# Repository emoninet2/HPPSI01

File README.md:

# HPPSI01

link to [HPPSI02](https://github.com/emoninet2/HPPSI02)

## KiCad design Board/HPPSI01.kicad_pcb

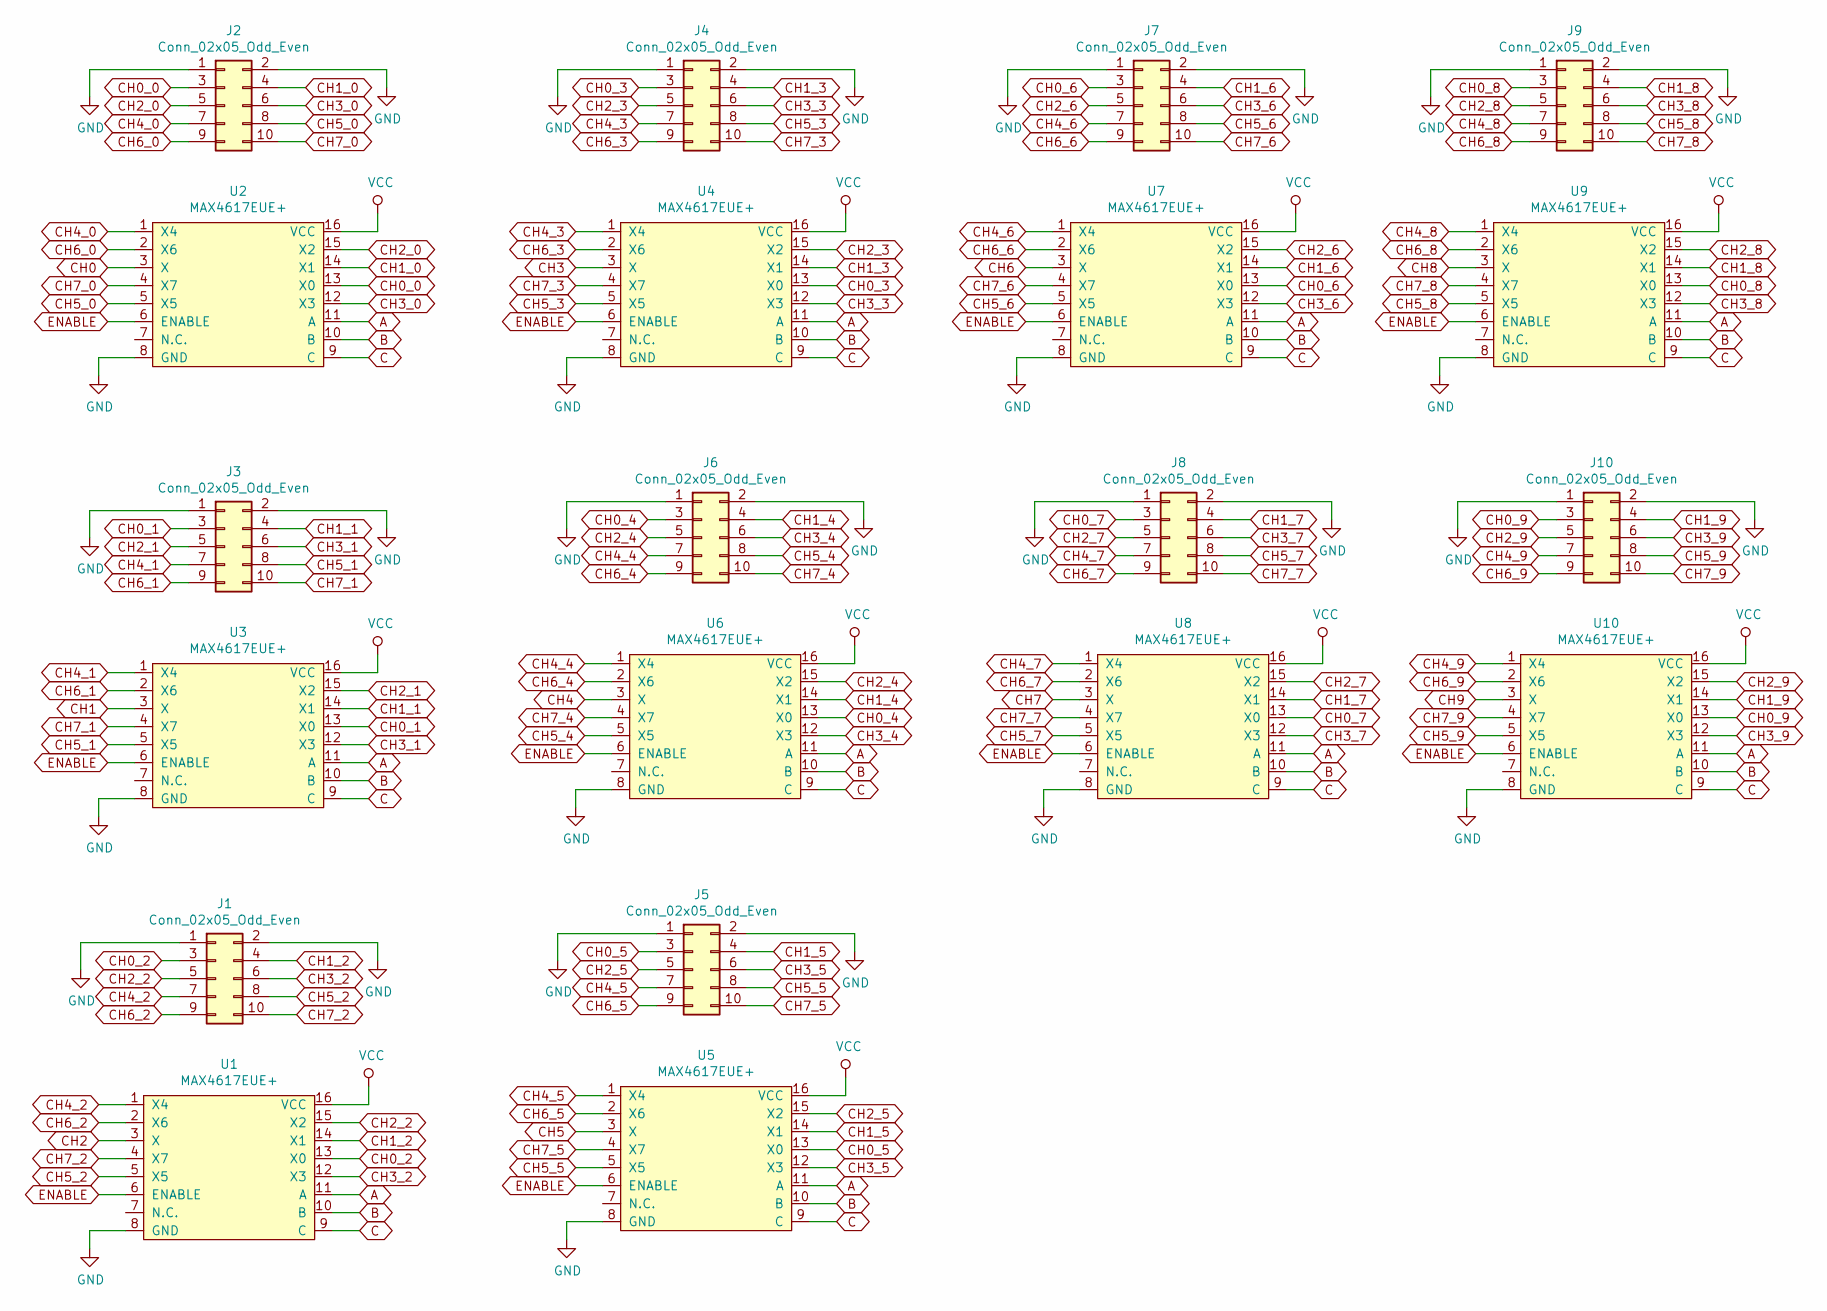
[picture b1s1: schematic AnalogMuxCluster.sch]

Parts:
J1, J2, J3, J4, J5, J6, J7, J8, J9, J10: Conn_02x05_Odd_Even; PinHeader_2x05_P2.54mm_Vertical
U1, U2, U3, U4, U5, U6, U7, U8, U9, U10: MAX4617EUE+; TSSOP-16_4.4x5mm_P0.65mm

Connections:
5V_CoraZ7: U1.16 (VCC), U2.16 (VCC), U3.16 (VCC), U4.16 (VCC), U5.16 (VCC), U6.16 (VCC), U7.16 (VCC), U8.16 (VCC), U9.16 (VCC), U10.16 (VCC); also elsewhere on the board
A: U1.11 (A), U2.11 (A), U3.11 (A), U4.11 (A), U5.11 (A), U6.11 (A), U7.11 (A), U8.11 (A), U9.11 (A), U10.11 (A)
B: U1.10 (B), U2.10 (B), U3.10 (B), U4.10 (B), U5.10 (B), U6.10 (B), U7.10 (B), U8.10 (B), U9.10 (B), U10.10 (B)
C: U1.9 (C), U2.9 (C), U3.9 (C), U4.9 (C), U5.9 (C), U6.9 (C), U7.9 (C), U8.9 (C), U9.9 (C), U10.9 (C)
CH0: U2.3 (X); also elsewhere on the board
CH0_0: J2.3, U2.13 (X0)
CH0_1: J3.3, U3.13 (X0)
CH0_2: J1.3, U1.13 (X0)
CH0_3: J4.3, U4.13 (X0)
CH0_4: J6.3, U6.13 (X0)
CH0_5: J5.3, U5.13 (X0)
CH0_6: J7.3, U7.13 (X0)
CH0_7: J8.3, U8.13 (X0)
CH0_8: J9.3, U9.13 (X0)
CH0_9: J10.3, U10.13 (X0)
CH1: U3.3 (X); also elsewhere on the board
CH1_0: J2.4, U2.14 (X1)
CH1_1: J3.4, U3.14 (X1)
CH1_2: J1.4, U1.14 (X1)
CH1_3: J4.4, U4.14 (X1)
CH1_4: J6.4, U6.14 (X1)
CH1_5: J5.4, U5.14 (X1)
CH1_6: J7.4, U7.14 (X1)
CH1_7: J8.4, U8.14 (X1)
CH1_8: J9.4, U9.14 (X1)
CH1_9: J10.4, U10.14 (X1)
CH2: U1.3 (X); also elsewhere on the board
CH2_0: J2.5, U2.15 (X2)
CH2_1: J3.5, U3.15 (X2)
CH2_2: J1.5, U1.15 (X2)
CH2_3: J4.5, U4.15 (X2)
CH2_4: J6.5, U6.15 (X2)
CH2_5: J5.5, U5.15 (X2)
CH2_6: J7.5, U7.15 (X2)
CH2_7: J8.5, U8.15 (X2)
CH2_8: J9.5, U9.15 (X2)
CH2_9: J10.5, U10.15 (X2)
CH3: U4.3 (X); also elsewhere on the board
CH3_0: J2.6, U2.12 (X3)
CH3_1: J3.6, U3.12 (X3)
CH3_2: J1.6, U1.12 (X3)
CH3_3: J4.6, U4.12 (X3)
CH3_4: J6.6, U6.12 (X3)
CH3_5: J5.6, U5.12 (X3)
CH3_6: J7.6, U7.12 (X3)
CH3_7: J8.6, U8.12 (X3)
CH3_8: J9.6, U9.12 (X3)
CH3_9: J10.6, U10.12 (X3)
CH4: U6.3 (X); also elsewhere on the board
CH4_0: J2.7, U2.1 (X4)
CH4_1: J3.7, U3.1 (X4)
CH4_2: J1.7, U1.1 (X4)
CH4_3: J4.7, U4.1 (X4)
CH4_4: J6.7, U6.1 (X4)
CH4_5: J5.7, U5.1 (X4)
CH4_6: J7.7, U7.1 (X4)
CH4_7: J8.7, U8.1 (X4)
CH4_8: J9.7, U9.1 (X4)
CH4_9: J10.7, U10.1 (X4)
CH5: U5.3 (X); also elsewhere on the board
CH5_0: J2.8, U2.5 (X5)
CH5_1: J3.8, U3.5 (X5)
CH5_2: J1.8, U1.5 (X5)
CH5_3: J4.8, U4.5 (X5)
CH5_4: J6.8, U6.5 (X5)
CH5_5: J5.8, U5.5 (X5)
CH5_6: J7.8, U7.5 (X5)
CH5_7: J8.8, U8.5 (X5)
CH5_8: J9.8, U9.5 (X5)
CH5_9: J10.8, U10.5 (X5)
CH6: U7.3 (X); also elsewhere on the board
CH6_0: J2.9, U2.2 (X6)
CH6_1: J3.9, U3.2 (X6)
CH6_2: J1.9, U1.2 (X6)
CH6_3: J4.9, U4.2 (X6)
CH6_4: J6.9, U6.2 (X6)
CH6_5: J5.9, U5.2 (X6)
CH6_6: J7.9, U7.2 (X6)
CH6_7: J8.9, U8.2 (X6)
CH6_8: J9.9, U9.2 (X6)
CH6_9: J10.9, U10.2 (X6)
CH7: U8.3 (X); also elsewhere on the board
CH7_0: J2.10, U2.4 (X7)
CH7_1: J3.10, U3.4 (X7)
CH7_2: J1.10, U1.4 (X7)
CH7_3: J4.10, U4.4 (X7)
CH7_4: J6.10, U6.4 (X7)
CH7_5: J5.10, U5.4 (X7)
CH7_6: J7.10, U7.4 (X7)
CH7_7: J8.10, U8.4 (X7)
CH7_8: J9.10, U9.4 (X7)
CH7_9: J10.10, U10.4 (X7)
CH8: U9.3 (X); also elsewhere on the board
CH9: U10.3 (X); also elsewhere on the board
ENABLE: U1.6 (ENABLE), U2.6 (ENABLE), U3.6 (ENABLE), U4.6 (ENABLE), U5.6 (ENABLE), U6.6 (ENABLE), U7.6 (ENABLE), U8.6 (ENABLE), U9.6 (ENABLE), U10.6 (ENABLE)
GND: J1.1, J1.2, J2.1, J2.2, J3.1, J3.2, J4.1, J4.2, J5.1, J5.2, J6.1, J6.2, J7.1, J7.2, J8.1, J8.2, J9.1, J9.2, J10.1, J10.2, U1.8 (GND), U2.8 (GND), U3.8 (GND), U4.8 (GND), U5.8 (GND), U6.8 (GND), U7.8 (GND), U8.8 (GND), U9.8 (GND), U10.8 (GND); also elsewhere on the board

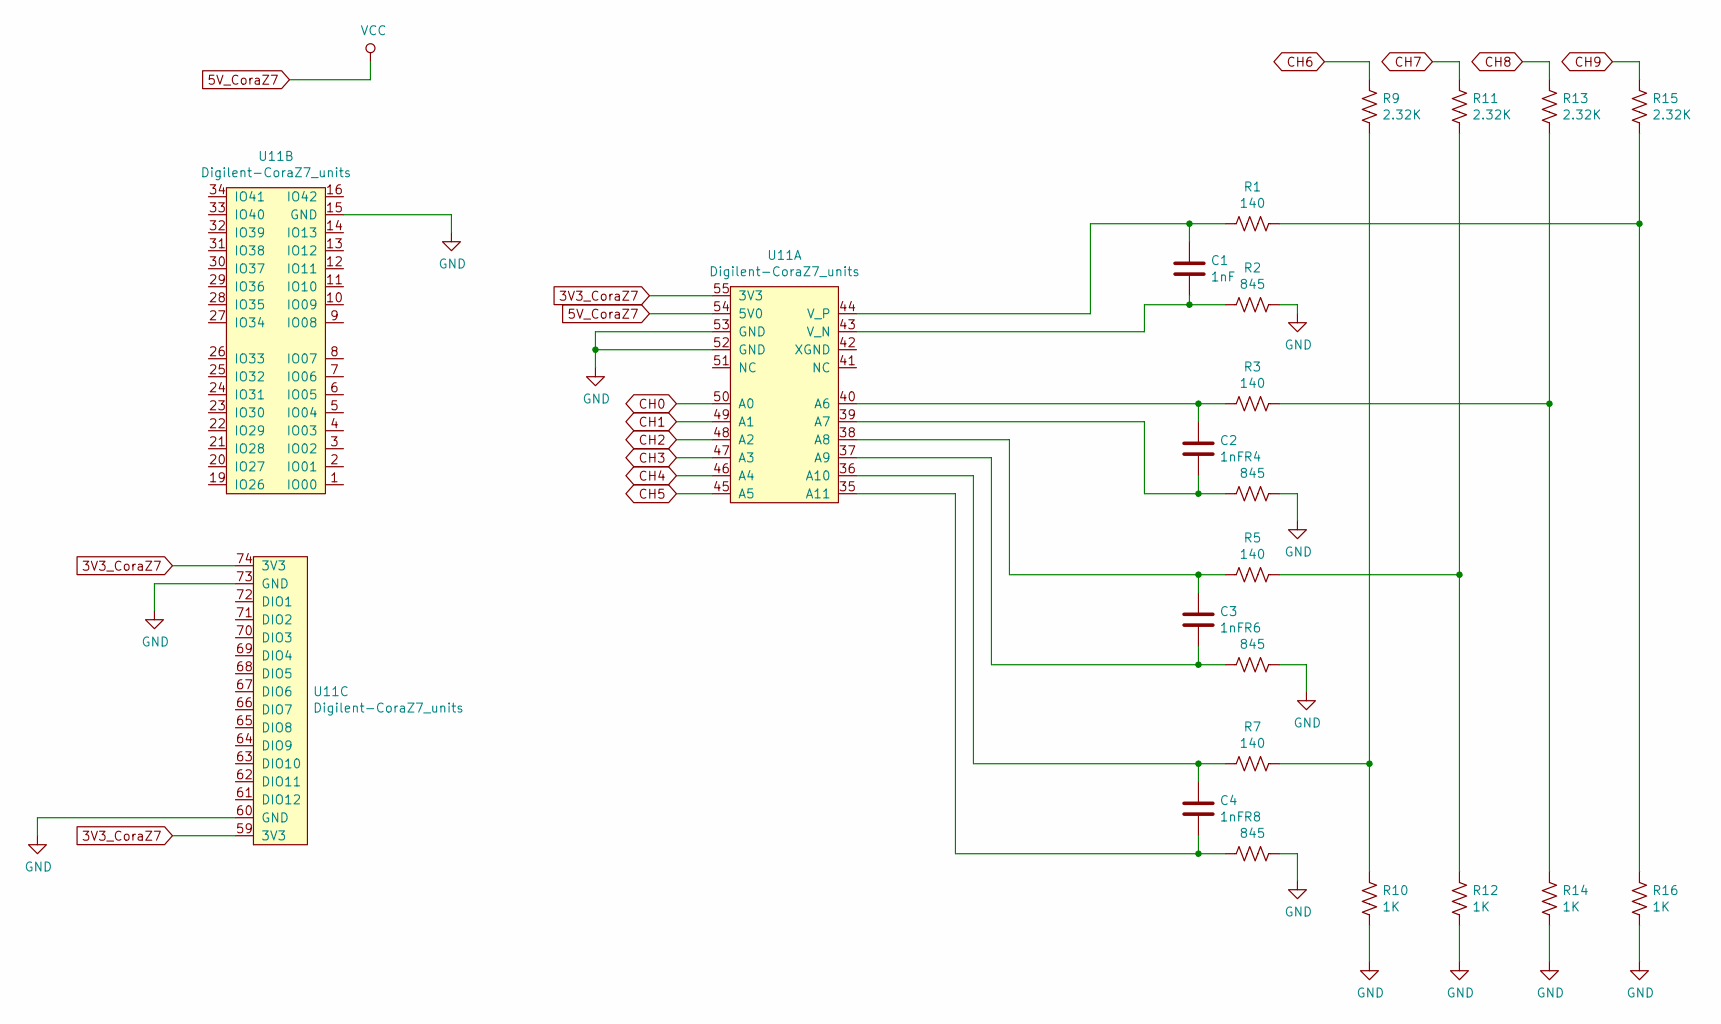
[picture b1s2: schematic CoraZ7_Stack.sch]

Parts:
C1, C2, C3, C4: 1nF; C_0402_1005Metric
R1, R3, R5, R7: 140; R_0402_1005Metric
R2, R4, R6, R8: 845; R_0402_1005Metric
R9, R11, R13, R15: 2.32K; R_0402_1005Metric
R10, R12, R14, R16: 1K; R_0402_1005Metric
U11: Digilent-CoraZ7_units; CoraZ7_stack

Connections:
3V3_CoraZ7: U11.55 (3V3), U11.59 (3V3), U11.74 (3V3)
5V_CoraZ7: U11.54 (5V0); also elsewhere on the board
CH0: U11.50 (A0); also elsewhere on the board
CH1: U11.49 (A1); also elsewhere on the board
CH2: U11.48 (A2); also elsewhere on the board
CH3: U11.47 (A3); also elsewhere on the board
CH4: U11.46 (A4); also elsewhere on the board
CH5: U11.45 (A5); also elsewhere on the board
CH6: R9.1; also elsewhere on the board
CH7: R11.1; also elsewhere on the board
CH8: R13.1; also elsewhere on the board
CH9: R15.1; also elsewhere on the board
GND: R2.2, R4.2, R6.2, R8.2, R10.2, R12.2, R14.2, R16.2, U11.15 (GND), U11.52 (GND), U11.53 (GND), U11.60 (GND), U11.73 (GND); also elsewhere on the board
unnamed: C1.1, R1.1, U11.44 (V_P)
unnamed: C1.2, R2.1, U11.43 (V_N)
unnamed: C2.1, R3.1, U11.40 (A6)
unnamed: C2.2, R4.1, U11.39 (A7)
unnamed: C3.1, R5.1, U11.38 (A8)
unnamed: C3.2, R6.1, U11.37 (A9)
unnamed: C4.1, R7.1, U11.36 (A10)
unnamed: C4.2, R8.1, U11.35 (A11)
unnamed: R1.2, R15.2, R16.1
unnamed: R7.2, R9.2, R10.1
unnamed: R5.2, R11.2, R12.1
unnamed: R3.2, R13.2, R14.1

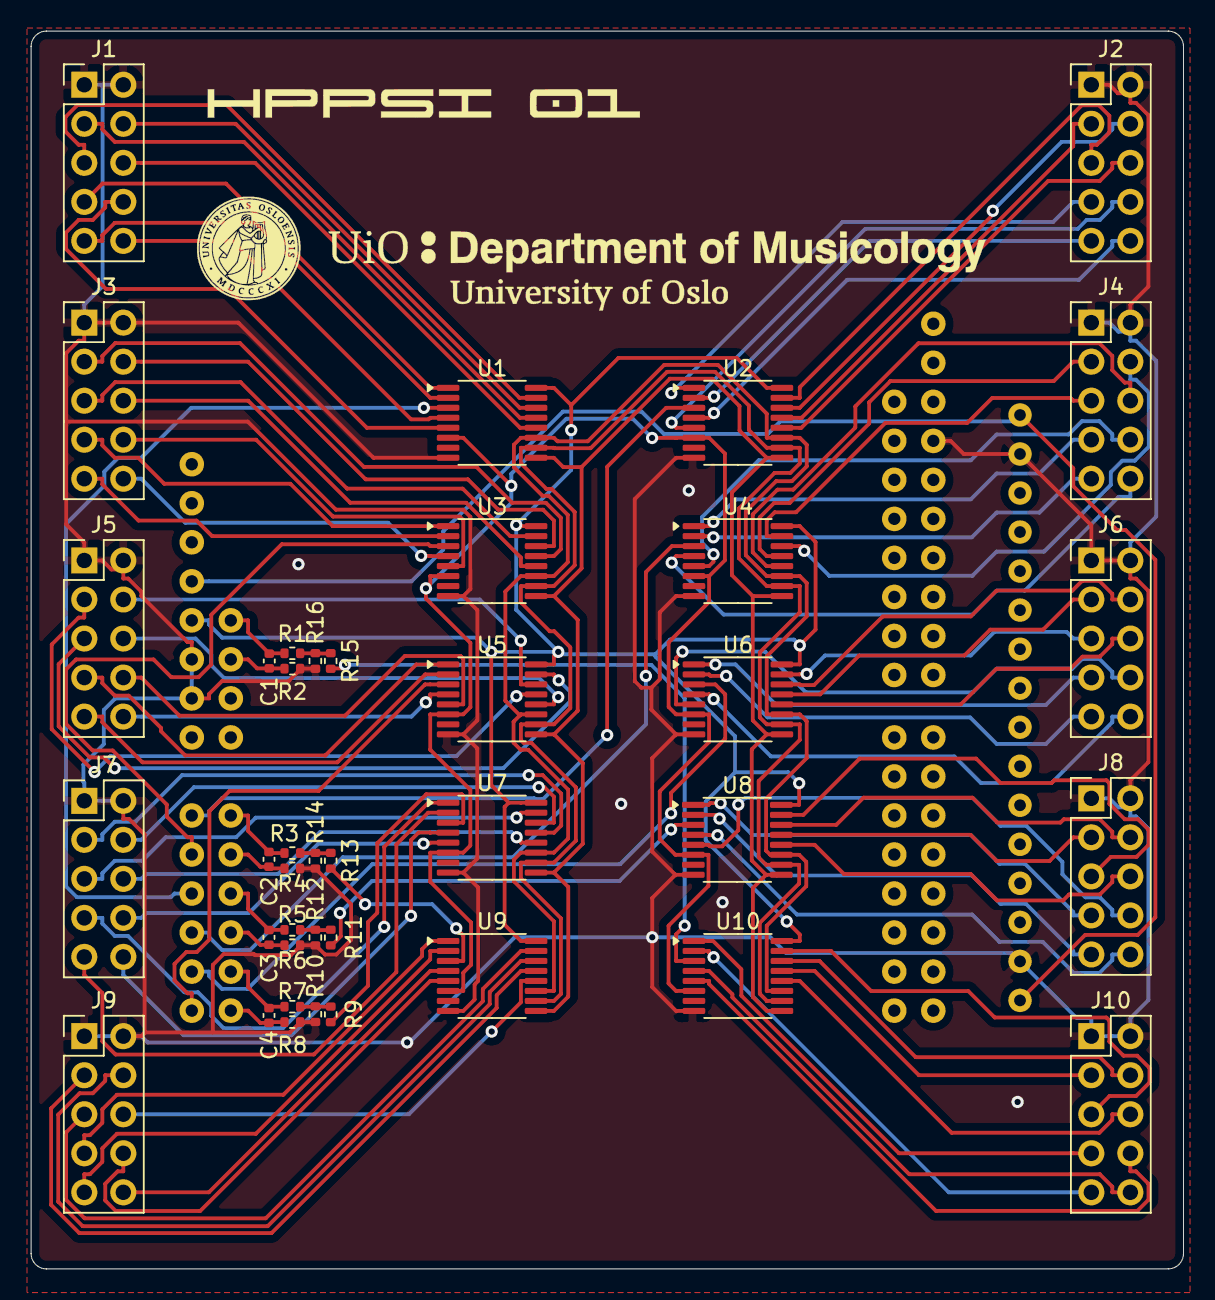
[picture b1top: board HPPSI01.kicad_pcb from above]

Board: 2 copper layers, 75.0 x 80.6 mm, 41 parts (0 on the bottom side), 109 nets.

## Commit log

2020-03-10 completed beta design
2020-03-10 reduced board size from top and bottom
2020-03-11 update copper pour
2020-05-29 added logo
2020-05-31 renamed project to HPPSI01
2020-10-08 added project software
2024-08-25 added 3D object in wrl format
